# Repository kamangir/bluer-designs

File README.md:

designs for [@sbc](https://github.com/kamangir/bluer-sbc) and [@ugv](https://github.com/kamangir/bluer-ugv).

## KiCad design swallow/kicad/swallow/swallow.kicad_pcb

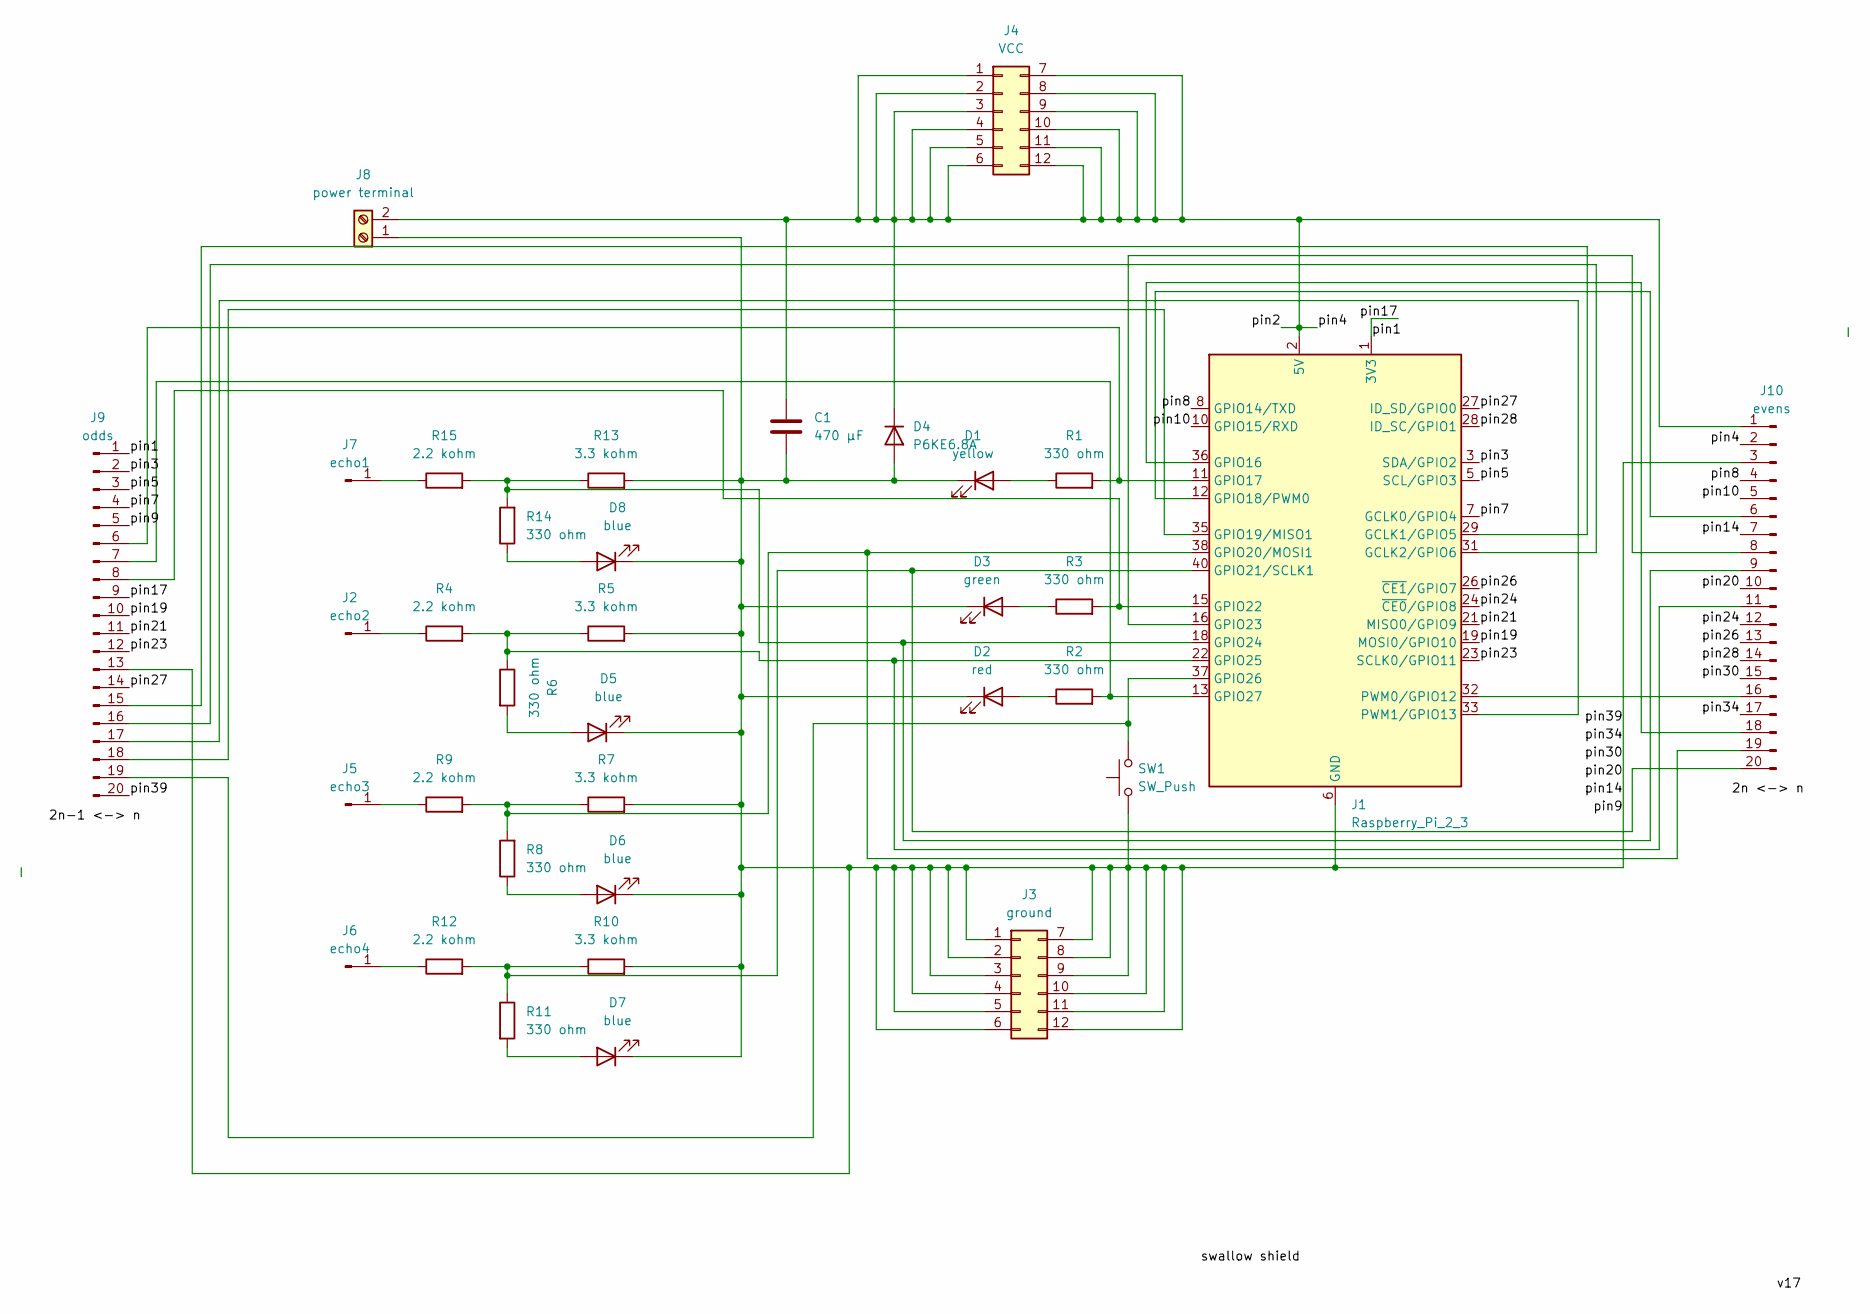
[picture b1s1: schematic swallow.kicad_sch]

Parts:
C1: 470 µF; CP_Radial_D8.0mm_P3.50mm
D1: yellow; LED_D5.0mm
D2: red; LED_D5.0mm
D3: green; LED_D5.0mm
D4: P6KE6.8A; D_DO-15_P10.16mm_Horizontal
D5, D6, D7, D8: blue; LED_D5.0mm
J1: Raspberry_Pi_2_3; PinSocket_2x20_P2.54mm_Vertical
J2: echo2; PinHeader_1x01_P2.54mm_Vertical
J3: ground; PinHeader_2x06_P2.54mm_Vertical
J4: VCC; PinHeader_2x06_P2.54mm_Vertical
J5: echo3; PinHeader_1x01_P2.54mm_Vertical
J6: echo4; PinHeader_1x01_P2.54mm_Vertical
J7: echo1; PinHeader_1x01_P2.54mm_Vertical
J8: power terminal; TerminalBlock_MaiXu_MX126-5.0-02P_1x02_P5.00mm
J9: odds; PinHeader_1x20_P2.54mm_Vertical
J10: evens; PinHeader_1x20_P2.54mm_Vertical
R1, R2, R3, R6, R8, R11, R14: 330 ohm; R_Axial_DIN0207_L6.3mm_D2.5mm_P10.16mm_Horizontal
R4, R9, R12, R15: 2.2 kohm; R_Axial_DIN0207_L6.3mm_D2.5mm_P10.16mm_Horizontal
R5, R7, R10, R13: 3.3 kohm; R_Axial_DIN0207_L6.3mm_D2.5mm_P10.16mm_Horizontal
SW1: SW_Push; SW_PUSH_6mm

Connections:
/pin1: J1.1 (3V3), J1.17 (3V3), J9.1, J9.9
/pin2: C1.1, D4.1 (K), J1.2 (5V), J1.4 (5V), J4.1, J4.2, J4.3, J4.4, J4.5, J4.6, J4.7, J4.8, J4.9, J4.10, J4.11, J4.12, J8.2, J10.1, J10.2
/pin3: J1.3 (SDA/GPIO2), J9.2
/pin5: J1.5 (SCL/GPIO3), J9.3
/pin7: J1.7 (GCLK0/GPIO4), J9.4
/pin8: J1.8 (GPIO14/TXD), J10.4
/pin10: J1.10 (GPIO15/RXD), J10.5
/pin14: C1.2, D1.1 (K), D2.1 (K), D3.1 (K), D4.2 (A), D5.1 (K), D6.1 (K), D7.1 (K), D8.1 (K), J1.6 (GND), J1.9 (GND), J1.14 (GND), J1.20 (GND), J1.25 (GND), J1.30 (GND), J1.34 (GND), J1.39 (GND), J3.1, J3.2, J3.3, J3.4, J3.5, J3.6, J3.7, J3.8, J3.9, J3.10, J3.11, J3.12, J8.1, J9.5, J9.13, J9.20, J10.3, J10.7, J10.10, J10.15, J10.17, R5.2, R7.2, R10.2, R13.2, SW1.1
/pin19: J1.19 (MOSI0/GPIO10), J9.10
/pin21: J1.21 (MISO0/GPIO9), J9.11
/pin23: J1.23 (SCLK0/GPIO11), J9.12
/pin24: J1.24 (~CE0/GPIO8), J10.12
/pin26: J1.26 (~CE1/GPIO7), J10.13
/pin27: J1.27 (ID_SD/GPIO0), J9.14
/pin28: J1.28 (ID_SC/GPIO1), J10.14
unnamed: D1.2 (A), R1.1
unnamed: D2.2 (A), R2.1
unnamed: D3.2 (A), R3.1
unnamed: D5.2 (A), R6.2
unnamed: D6.2 (A), R8.1
unnamed: D7.2 (A), R11.2
unnamed: D8.2 (A), R14.1
unnamed: J1.29 (GCLK1/GPIO5), J9.15
unnamed: J1.31 (GCLK2/GPIO6), J9.16
unnamed: J1.36 (GPIO16), J10.18
unnamed: J1.11 (GPIO17), J9.6, R1.2
unnamed: J1.12 (GPIO18/PWM0), J10.6
unnamed: J1.35 (GPIO19/MISO1), J9.18
unnamed: J1.38 (GPIO20/MOSI1), J10.19, R7.1, R8.2, R9.2
unnamed: J1.40 (GPIO21/SCLK1), J10.20, R10.1, R11.1, R12.2
unnamed: J1.15 (GPIO22), J9.8, R3.2
unnamed: J1.16 (GPIO23), J10.8
unnamed: J1.18 (GPIO24), J10.9, R13.1, R14.2, R15.2
unnamed: J1.22 (GPIO25), J10.11, R4.2, R5.1, R6.1
unnamed: J1.37 (GPIO26), J9.19, SW1.2
unnamed: J1.13 (GPIO27), J9.7, R2.2
unnamed: J1.32 (PWM0/GPIO12), J10.16
unnamed: J1.33 (PWM1/GPIO13), J9.17
unnamed: J2.1, R4.1
unnamed: J5.1, R9.1
unnamed: J6.1, R12.1
unnamed: J7.1, R15.1

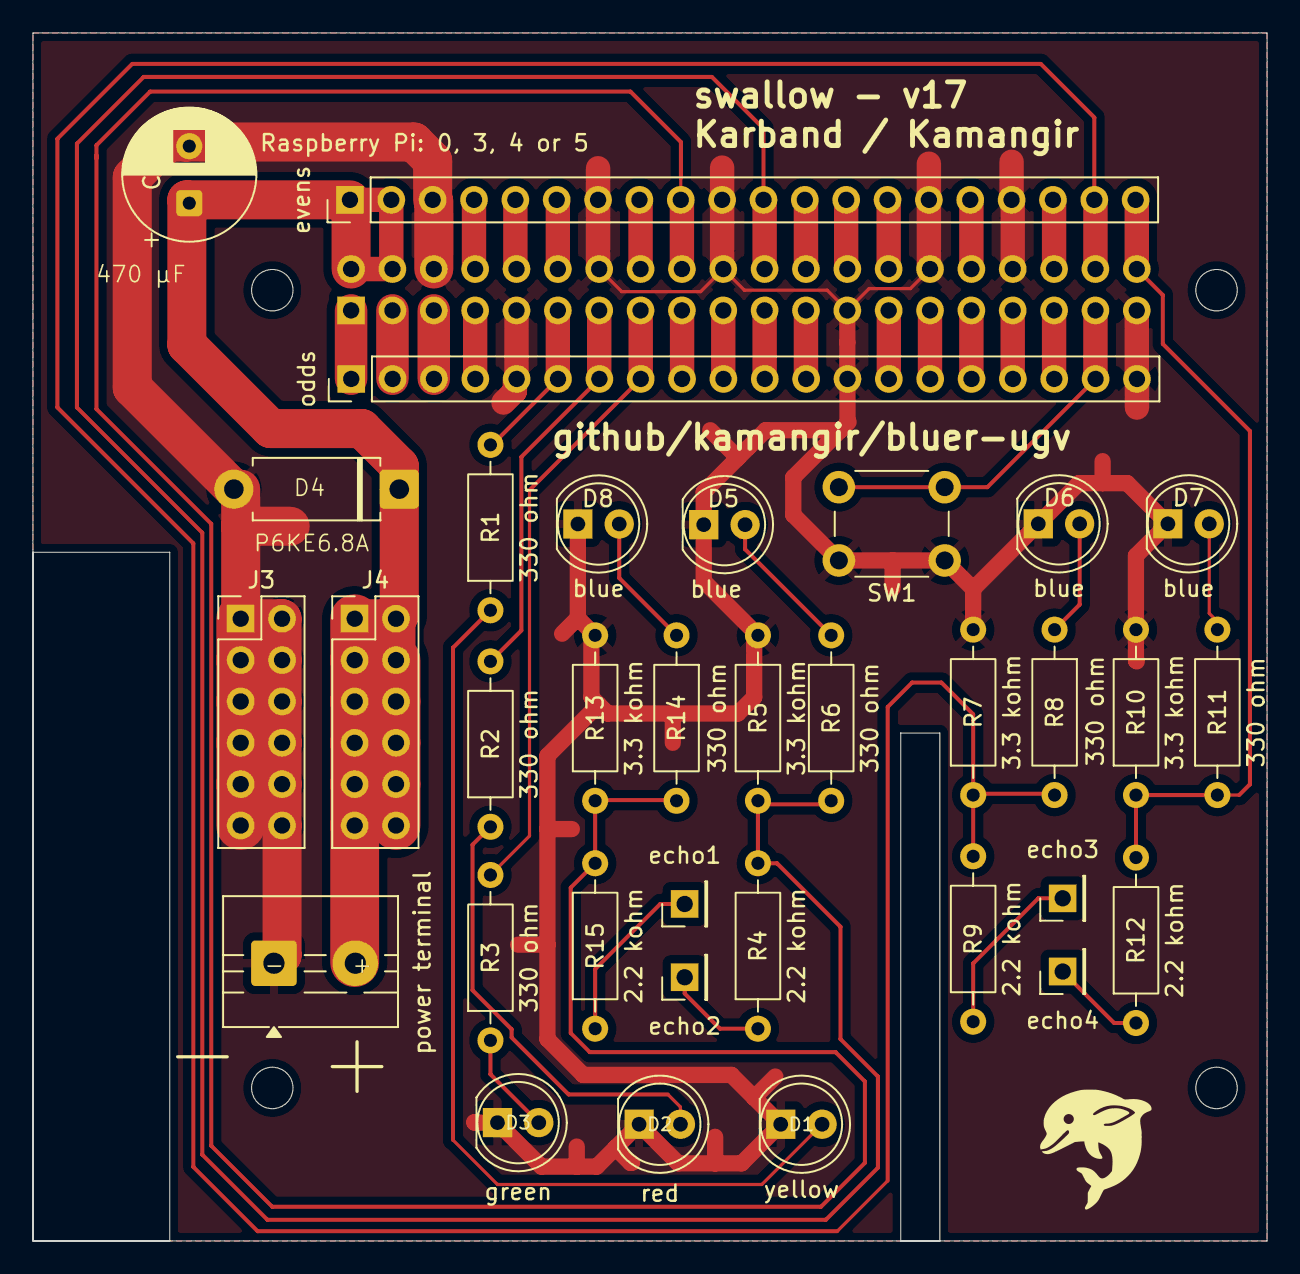
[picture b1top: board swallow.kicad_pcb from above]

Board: 2 copper layers, 75.8 x 74.2 mm, 35 parts (1 on the bottom side), 42 nets.

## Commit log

2025-08-25 ++ - kamangir/bolt#746
2025-08-26 + - kamangir/bolt#746
2025-09-28 doc++ - kamangir/bolt#746
2025-09-28 rebuild - kamangir/bolt#746
2025-10-01 += ultrasonic sensors 🪄 - kamangir/bolt#746
2025-10-05 +=kicad - kamangir/bolt#746
2025-10-05 sparrow -> arzhang - kamangir/bolt#746
2025-10-30 swallow PCB update - kamangir/bolt#746
2025-11-03 swallow gerber files - kamangir/bolt#746
2025-11-12 fix - kamangir/bolt#746
2025-11-19 rangin refactors - kamangir/bolt#746
2025-11-28 2-headed arzhang - kamangir/bolt#746
2025-12-05 += DSN-VC288 - kamangir/bolt#746
